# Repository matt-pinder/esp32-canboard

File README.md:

# ESP32-CANBoard
* ESP32-S3 Dual Core SoC
* MCP2562T CAN Transceiver (up to 1Mbps)
* 10x 5v Tolerant Inputs - Pressure Sensors, NTCs, etc
* 2x 5v Outputs - Fused at 500mA (Thermal Reset)
* USB-C for programming, with JTAG support for debugging
* ESD Protection on both USB and CAN
* JAE Automotive Connector (PCB Socket: MX23A18NF1, Cable Plug: MX23A18SF1)
* Optional pull-up resistors via fused 5v rail for each input (TH 6.3mm)
* Optional 120ohm CAN terminating resistor
* Configuration via web interface over WiFi
* Optional per-channel median filtering with selectable strength (none/low/med/high) to reduce noise
* Small PCB Footprint - 40mm x 60mm

## Build requirement

This project targets ESP-IDF 6.0.2. Activate the 6.0.2 environment before running any `idf.py` command; `main/idf_component.yml` and `dependencies.lock` enforce that toolchain version.

## Device Configuration

The board keeps its WiFi access point available continuously. To reduce idle memory use, the web server starts when a client associates with the access point and stops when that client disconnects.

Copy `main/inc/secrets.example.h` to the ignored `main/inc/secrets.h` and define infrastructure credentials with `KNOWN_WIFI_NETWORKS(X)`. Networks are tried in list order when ESP-NOW is disabled; the configuration access point remains available throughout.

| SSID | WPA2 Key | Web UI |
|:---|:---|:---|
| ESP32-CanBoard | canconfig | http://192.168.4.1 |

The web UI allows you to:

- View and edit per-channel settings (name, sensor type, pull-up, **filter level** dropdown, pressure calibration).
- Configure required CAN parameters - Base ID and bus speed.
- Configure CAN and ESP-NOW output, including optional CAN bus relay over ESP-NOW.
- Define reusable global Conditions from local sensor values or DBC-imported CAN signals, then reference those booleans from multiple Outputs and Triggered timers.
- Configure up to 8 Outputs using local sensor values, DBC-imported CAN signals, Conditions, startup timers, inline edge-triggered timers, PULSE lookup tables, and PWM duty lookup tables.
- Adjust pullup vref calculation voltage to allow for LDO regulator output/load.
- View current input voltages and calculated values in real time.
- Backup the entire configuration to a JSON file.
- Restore configuration from a previously exported JSON file.

| Function | Description |
|:----|:----|
| Save Config | Save current UI settings to the dedicated `config` NVS partition. Changes are validated, persisted and applied immediately. |
| Capture CAN (10s) | Stream every physical CAN data/RTR frame to the browser as a compact `.canlog` download. The board uses a bounded RAM queue and does not write the capture to flash. |
| Backup | Download one JSON snapshot containing the board configuration, reusable Conditions and Outputs. The filename is prefixed with `esp32-canboard-config-` and suffixed with the client timestamp in `ddmmyy-hhmmss` format. |
| Restore | Select a previously exported JSON file. The backend validates and applies the board configuration, Conditions and Outputs together while retaining their separate flash records. Legacy `rules` data is never imported. |
| Reboot Device | Reboots the device. |

**Notes:**
- CAN captures use a versioned little-endian binary format with a fixed header,
  20-byte frame records and a final loss/error trailer. Convert a downloaded
  capture to candump-style text with
  `python3 tools/decode_can_capture.py capture.canlog`, or add
  `--format csv -o capture.csv` for CSV. A missing `CANEND1` trailer means the
  browser connection ended before the capture completed.
- Board configuration is persisted as one current record in the dedicated `config` NVS partition. Conditions and Outputs are persisted together in the existing CRC-checked raw `rules` partition with atomic A/B writes; the partition location is unchanged even though the user-facing feature is now named Outputs.
- Only the current version-15 NVS board record is accepted. Pre-v15 NVS records and `/spiffs/config.bin` are deliberately unsupported after the verified 2026-10-05 aggregate backup.
- Normal `idf.py flash` updates the application and SPIFFS web assets, but does not write the dedicated `config` partition.
- `erase-flash`, whole-chip images, or explicitly flashing address `0x200000` will still erase configuration; ordinary application/partition-table flashing will not.
- After restoring a new configuration via the web UI the changes are applied immediately.
- The current checked-in recovery export is `config/esp32-canboard-config-051026-090441.json` (SHA-256 `25cc3a9ffa824093bf31c163345749b8048a588224715e386e33c09e3a9b6c78`). It contains all ten channels, two ESP-NOW clients, current GPS-source fields, Output schema version 4, one Condition, and three configured Outputs.

## Wi-Fi OTA

The VS Code custom task runs `scripts/build_and_ota.sh`. The script first checks
`/api/status`, rebuilds when either OTA artifact is missing or the sources are
newer, regenerates the embedded web asset as part of that build, and then
uploads both `build/esp32-canboard.bin` to `/api/ota` and `build/spiffs.bin` to
`/api/spiffs`. Connect to the `ESP32-CanBoard` access point before using the
default URL.

Set `ESP32_CANBOARD_OTA_URL` to override the target, for example:

```sh
ESP32_CANBOARD_OTA_URL=http://192.168.4.1/api/ota scripts/build_and_ota.sh
```

Set `ESP32_CANBOARD_SPIFFS_URL` as well only when the SPIFFS endpoint does not
share the application OTA host. The SPIFFS image must exactly match the existing
partition size and is SHA-256 checked in PSRAM before its partition is erased.
It is then written, read back and remounted. The HTTP API remains available if
SPIFFS cannot mount, allowing the image upload to be retried OTA.

The first combined OTA run from legacy firmware uploads the new application
first, waits for `/api/spiffs` to become available after reboot, and then sends
the web assets. Later runs send SPIFFS first and the application second, so only
the application update requires a reboot. No partition-table change or cable
flash is required when the installed firmware already supports `/api/ota`.

OTA requires the dual-slot partition table. After this change, perform one
normal UART `idf.py flash` only if the installed board does not already have
that table. The existing SPIFFS, `config`, and `rules` partition offsets are
unchanged; erasing the flash or writing those data offsets explicitly does not
preserve their contents.

## CAN Output

The device transmits five input-data frames followed by two Output command frames starting at the configured base ID. All frames use standard 11-bit CAN identifiers and DLC 8. Because the two Output frames occupy `Base ID + 5` and `Base ID + 6`, the configurable CAN base ID is restricted to `0x000` through `0x7F9`.

| CAN ID | Name | Payload |
|:---|:---|:---|
| Base ID | analogVoltage_1 | Inputs 0..3 as four uint16 (LSB,MSB) — bytes 0..7 (values in mV) |
| Base ID + 1 | analogVoltage_2 | Inputs 4..7 as four uint16 (LSB,MSB) — bytes 0..7 (values in mV) |
| Base ID + 2 | analogVoltage_3 | Inputs 8..9 as two uint16 (bytes 0..3), dynamic0 (bytes 4..5), dynamic1 (bytes 6..7) |
| Base ID + 3 | dynamicSignals_1 | dynamic2, dynamic3, dynamic4, dynamic5 as four 2-byte values (bytes 0..7) |
| Base ID + 4 | dynamicSignals_2 | dynamic6, dynamic7, dynamic8, dynamic9 as four 2-byte values (bytes 0..7) |
| Base ID + 5 | OutputBinaryCommands | Eight state bits, eight validity bits, eight pulse-mode bits, rolling counter, protocol version 2 |
| Base ID + 6 | OutputDutyCommands | Eight packed 7-bit duty percentages and the matching rolling counter |

The two Output frames are generated from one engine evaluation and one rolling counter. They are emitted in the order `Base + 5`, then `Base + 6`, after the five sensor frames at the configured 25 Hz or 50 Hz rate. When physical CAN is enabled both frames are sent to CAN, and both are also sent to every ESP-NOW client. The two Output CAN IDs are reserved: externally received frames colliding with either ID are not accepted as Output source data and are not re-relayed.

Encoding rules for dynamic values (one per input):

| Channel | Type | Encoding |
|:---|:---|:---|
|analogVoltage|-|unsigned uint16 = voltage * 1000 (resolution 0.001 V)|
|dynamicSignal|Raw|unsigned uint16 = **0** use analogVoltage signal instead|
|dynamicSignal|Pressure|unsigned uint16 = pressure_kPa * 100 (resolution 0.01 kPa)|
|dynamicSignal|NTC|signed int16 = temperature_C * 1 (°C as integer)|

Example DBCs for signal names and scaling are [dbc/esp32-canboard.dbc](dbc/esp32-canboard.dbc) and [dbc/esp32-canboard-outputs.dbc](dbc/esp32-canboard-outputs.dbc). The web UI also generates an Output DBC using the current base ID and configured Output labels.

### Outputs

There are eight configurable Outputs. Ordered cases retain the existing first-match `IF` / `ELSE IF` behavior; tests within one case are ANDed, while additional cases provide OR-through-ELSE-IF behavior. The tests only select which case runs: a matching PULSE case still derives its ON/OFF phase from the pulse lookup, and a matching PWM case still derives duty from the PWM lookup (with binary `state=1` only at exactly 100% duty). Existing OFF, ON, and PULSE actions retain their binary behavior. PWM is a fourth action and has its own numeric duty value; it does not replace or reinterpret the binary state, valid, or pulse signals.

For each timed PULSE lookup row, the cycle period must be greater than zero and the ON time must be between zero and the cycle period inclusive. `ON time = 0` means continuously OFF for that lookup point. The web editor exposes a dedicated `Permanently ON at/above` threshold instead of requiring a magic-looking final `ON time = cycle period` row. When configured, the UI stores that threshold as the final 1 s ON / 1 s period point in the existing PULSE lookup format, so no protocol or configuration-version change is required. Values at and above that threshold remain continuously ON.

Each PWM case selects one lookup source, a source hysteresis, and one through eight `{input_value, duty_percent}` rows. Input values must be finite and strictly increasing, and duties must be integer percentages from 0 through 100. Values below or above the lookup range clamp to the nearest endpoint. Values between rows are linearly interpolated and rounded to the nearest percentage. Duty is calculated immediately when a PWM case is entered, then held until the source differs from the accepted lookup input by **more than** the configured hysteresis. Entering another case, replacing configuration, startup, or source invalidation resets that PWM runtime state.

Source freshness and zero-confirmation rules apply equally to tests, PULSE lookup sources, and PWM lookup sources. A missing, stale, or not-yet-confirmed PWM source publishes `valid=0`, `state=0`, `pulse=0`, and duty `0`.

### Conditions

Up to 16 reusable named **Conditions** can be defined once and referenced by any Output case or Triggered timer. A Condition has one local-sensor or DBC-imported CAN source, a comparison and threshold, optional hysteresis, and a boolean result. Runtime state keeps `value` and `valid` separate: a Condition can therefore be `true`, `false`, or invalid. This avoids repeating CAN message/signal/comparison settings across multiple Outputs and reduces the chance of small configuration differences between rules.

Each Condition also defines what to do when its source later becomes unavailable or stale: `Invalid`, `False`, `True`, or `Hold last`. The stale policy is deliberately ignored until the Condition has first been established from at least one valid source sample. For example, `Engine running = DME1.RPM >= 600` with `When source stale = False` behaves as follows:

```text
Boot with no RPM ever received  -> Engine running is invalid
RPM received at 1000            -> Engine running = true
RPM CAN then disappears         -> Engine running = false
```

That distinction means ECU silence after a known-running engine can be used as a shutdown event without treating a board boot where the ECU was never present as an engine shutdown. A normal Output Condition test chooses whether the named Condition must be `True` or `False`; an invalid Condition retains the existing ordered-case unknown/invalid behavior rather than silently becoming false.

#### `Base ID + 5`: binary Output frame

Protocol version 2 keeps binary state, validity, and pulse mode independent. Only the low byte of each former 16-bit mask is used; the upper byte is required to be zero.

| Bytes | Encoding | Meaning |
|:---|:---|:---|
| 0 | uint8 bitmask | Output 1..8 state bits |
| 1 | uint8 | Reserved, must be `0` |
| 2 | uint8 bitmask | Output 1..8 validity bits |
| 3 | uint8 | Reserved, must be `0` |
| 4 | uint8 bitmask | Output 1..8 PULSE-mode bits |
| 5 | uint8 | Reserved, must be `0` |
| 6 | uint8 | Rolling counter, wraps `255 -> 0` |
| 7 | uint8 | Protocol version, exactly `2` |

For one Output, the action semantics are:

| Action / condition | state | valid | pulse | duty |
|:---|:---:|:---:|:---:|:---:|
| OFF | 0 | 1 | 0 | 0 |
| ON | 1 | 1 | 0 | 0 |
| PULSE, currently OFF | 0 | 1 | 1 | 0 |
| PULSE, currently ON | 1 | 1 | 1 | 0 |
| PWM, duty 0..99% | 0 | 1 | 0 | 0..99 |
| PWM, duty exactly 100% | 1 | 1 | 0 | 100 |
| Invalid / stale | 0 | 0 | 0 | 0 |

For OFF/ON/PULSE consumers, the safe applied binary state remains:

```text
applied binary state = valid AND state
```

For PWM, `state` is **not** a PWM-enabled flag. It is `1` only when the calculated duty is exactly 100%; duty 0 through 99 publishes `state=0`. Downstream configuration determines whether an Output should consume the duty field.

Examples for an otherwise empty binary frame (`CC` is the shared rolling counter):

| Situation | state / valid / pulse | `Base + 5` data bytes |
|:---|:---|:---|
| Output 1 continuously ON | `1 / 1 / 0` | `01 00 01 00 00 00 CC 02` |
| Output 1 validly OFF | `0 / 1 / 0` | `00 00 01 00 00 00 CC 02` |
| Output 2 in PULSE ON phase | `1 / 1 / 1` | `02 00 02 00 02 00 CC 02` |
| Output 2 in PULSE OFF phase | `0 / 1 / 1` | `00 00 02 00 02 00 CC 02` |
| Output 1 PWM at 50% | `0 / 1 / 0` | `00 00 01 00 00 00 CC 02` |
| Output 1 PWM at 100% | `1 / 1 / 0` | `01 00 01 00 00 00 CC 02` |
| Output invalid | `0 / 0 / 0` | `00 00 00 00 00 00 CC 02` |

#### `Base ID + 6`: duty frame

The duty frame packs eight unsigned 7-bit fields into bits 0 through 55. Values 101 through 127 are malformed and must be rejected by a consumer.

| Output | Start bit | Length | Valid values |
|:---:|:---:|:---:|:---:|
| 1 | 0 | 7 | 0..100 |
| 2 | 7 | 7 | 0..100 |
| 3 | 14 | 7 | 0..100 |
| 4 | 21 | 7 | 0..100 |
| 5 | 28 | 7 | 0..100 |
| 6 | 35 | 7 | 0..100 |
| 7 | 42 | 7 | 0..100 |
| 8 | 49 | 7 | 0..100 |
| Counter | 56 | 8 | 0..255 |

OFF, ON, and PULSE actions always publish duty `0`. Only the selected PWM action publishes a 0..100 value, and invalid PWM Outputs publish `0`. For example, Output 1 at 50% produces `32 00 00 00 00 00 00 CC`; Output 1 at 100% produces `64 00 00 00 00 00 00 CC`. A cross-byte example with duties `{0, 1, 99, 100, 1, 99, 100, 0}` produces `80 C0 98 1C 18 93 01 CC`.

A PWM consumer must treat `Base + 5` and `Base + 6` as one paired command. Accept duty only when both frames are correctly formed, both are fresh according to the consumer's timeout policy, and both counters match. A malformed frame, protocol-version error, duty outside 0..100, counter mismatch, or stale/missing partner must force applied duty to zero. Counter wrap from `255` to `0` is normal.

### Output timers

`Startup timer` is the original milliseconds-since-boot test. `Triggered timer` is an inline Output test and can be driven either directly from a local/CAN source or from a reusable Condition.

For a raw local/CAN trigger, the timer uses the configured comparison, threshold and optional hysteresis. It first has to observe that trigger false, which arms it; the next false-to-true transition starts the configured active period. Once active, the timer remains true until the period expires even if the raw trigger CAN source subsequently becomes stale or disappears.

For a Condition trigger, the editor selects a named Condition and whether the timer should trigger when it becomes `True` or `False`. The timer again arms only after first observing the opposite valid state. This combines with the Condition stale policy to handle ECUs that stop broadcasting before sending a low shutdown RPM. For example:

```text
Condition: Engine running
  DME1.RPM >= 600
  When source stale: False

Triggered timer:
  Engine running becomes False
  Active for 300 seconds
```

If the engine was observed running and its RPM broadcast then disappears, `Engine running` becomes false and the 300-second timer starts. If the board has never received a valid RPM sample, the Condition remains invalid and the timer does not arm or trigger.

Other AND tests remain live while a timer is active, so `OilTemp > 100 AND [Engine running becomes false, active for 300 s] -> ON` turns off early if oil temperature falls below the threshold, while the 300-second timer itself continues counting. Triggered timers are updated for every enabled Output before ordered case selection, so a timer in a lower-priority ELSE-IF case can still start while an earlier case is currently winning.

### Output configuration compatibility

The aggregate JSON property remains `outputs`, now at configuration version `5`. The schema contains `signal_timeout_ms`, used CAN `sources`, a sparse `conditions` array numbered 1 through 16, and a sparse `outputs` array numbered 1 through 8. CAN sources can carry DBC-derived physical range and raw-invalid-value metadata. Conditions serialize `label`, `source_name`, comparison/hysteresis fields, and `stale_behavior`. Output Condition tests reference the Condition by name; Condition-driven Triggered timers serialize `trigger_condition_name`, the expected boolean state, and `trigger_duration_ms`. Raw-source Triggered timers retain their direct `source_name`, comparison/hysteresis and duration fields. PWM cases continue to serialize `pwm_source_name`, `pwm_hysteresis`, and `pwm_points`.

Version 4 JSON imports and compact raw-partition records remain accepted. Their CAN sources migrate with validity checks disabled until a reference DBC is selected and Outputs are saved. Version 5 records persist the DBC range and `GenSigInvalidValue` metadata in the same CRC-checked A/B record as Outputs, Conditions and CAN sources. Frames carrying an invalid raw value or a decoded value outside the enabled range do not replace the last accepted value or refresh its timestamp, allowing the configured stale behavior (including `Hold last`) to take effect after `signal_timeout_ms`. No partition-table change is required.

Pre-Output rule records remain deliberately incompatible and are not translated: on first boot with one of those old records, firmware initializes eight empty Outputs and no Conditions and commits the empty current record into both CRC-checked A/B slots. The physical raw partition remains named `rules` and remains at the same partition-table location.

Aggregate restore requires a valid current `outputs` object. Missing, malformed, or incompatible Output data and invalid CAN base IDs are rejected rather than reset, clamped, guessed, or translated. Legacy top-level `rules` backups are unsupported.

Live status is exposed as `/api/live_values.conditions` for configured Conditions and `/api/live_values.outputs` for configured Outputs. Condition status includes boolean value, validity, whether a valid source has ever established the Condition, source freshness and source-invalid reason. Output live status still includes `duty_percent` for the selected valid PWM case.

### E46 M3 MK60 cluster emulator (capture-first)

The firmware contains an opt-in MK60 request/response service for cars where
the original instrument cluster has been removed. It is disabled by default
and has no factory response payload: capture the car first with the standalone
listen-only logger in [`tools/mk60-can-capture`](tools/mk60-can-capture).

The `mk60_emulator` object is included in configuration backup/import JSON. A
profile contains the exact standard data frames observed after the MK60's
standard `0x610` RTR request. Only `0x610`, `0x613`, `0x615`, `0x316`, and
`0x329` are accepted, the first response must be `0x610`, and emulation can
only be enabled with a complete profile at 500 kbit/s.

```json
"mk60_emulator": {
  "enabled": false,
  "trigger_id": 1552,
  "trigger_dlc": 8,
  "responses": []
}
```

Populate `responses` from repeatable connected/disconnected captures. Each
entry has `id`, `dlc`, `delay_before_ms`, and an eight-element `data` byte
array. Do not copy example payloads from the internet or enable the feature
until the bytes and timing have been verified on the target MK60. A CAN
transmit error or bus-off condition latches the emulator off until its profile
is reapplied or the board restarts.

### CAN relay over ESP-NOW

When ESP-NOW and **Relay CAN bus** are enabled for a client, externally received CAN frames are encoded into the same portable raw-CAN batch protocol as the board's own frames. The wire format is not an in-memory `twai_message_t`: version 1 uses a 14-byte little-endian header followed by one to eighteen fixed 13-byte CAN records, for a maximum packet size of 248 bytes. Physical CAN transmission of the board's own sensor frames may remain disabled; the TWAI controller and CAN speed setting remain active while relay reception, MK60 emulation, or externally sourced Output rules need CAN input.

Relay traffic is best-effort and lower priority than the board's sensor and GPS output. The bounded 128-frame queue discards its oldest frame when full instead of blocking ADC sampling or locally generated transmissions. Frames are batched for up to 5 ms. Each client has its own sequence and delivery state; after three consecutive delivery failures only that client backs off to one probe per second, while healthy clients continue at normal rate.

Each configured ESP-NOW client can also have an optional human-readable label. The label is persisted with the board configuration and included in configuration export/import JSON alongside that client's MAC address and relay setting. Existing configurations migrate with blank client labels.

ESP-NOW and the local configuration access point use Wi-Fi channel 1. The receiving ESP-NOW device must also operate on channel 1 and must give this board its station MAC as the permitted sender. Configure the receiver's station MAC as a client here; enable **Relay CAN bus** for that client only when physical CAN frames received by this board must also reach it. Locally generated sensor, Output, and GPS frames are sent to every configured client. ESP-NOW is unencrypted, so receiver MAC filtering rejects unrelated senders but is not cryptographic authentication.

While ESP-NOW is enabled, this firmware deliberately keeps the station radio on channel 1 and does not join a configured infrastructure network. The configuration SoftAP remains available and owns the fixed radio channel.

### Connected repository contract

| Repository | Role | ESP-NOW/CAN requirement |
|:---|:---|:---|
| `esp32-r8` | R8 dashboard/logger | Add its reported station MAC as a client; it defaults to permitting canboard STA MAC `DC:DA:0C:3B:B2:0C`. It decodes classic standard, non-RTR data frames only. |
| `esp32-e36` | E36 dashboard/logger | Add its reported station MAC as a client; it defaults to permitting canboard STA MAC `DC:DA:0C:3C:E8:08`. It decodes classic standard, non-RTR data frames only. |
| `esp32-output` | Output/PWM receiver and optional GPS responder | Add its displayed station MAC as a client. Output command frames use `Base + 5` and `Base + 6`; GPS response uses the separate 44-byte `GP` version-1 snapshot. |

The raw-CAN batch format is version 1 in all four repositories. Dashboard DBCs, telemetry schemas, RTCs, UI projects, hardware pins, NVS namespaces, and default sender MACs are vehicle profiles and are intentionally not interchangeable.

## Dragy GPS Output

When GPS is enabled, the board scans for the configured Dragy BLE MAC, connects to service `FD00`, performs the `FD03` challenge response, and decodes checksum-valid UBX NAV-PVT packets from `FD02`. Valid fixes are published at the GPS update rate; a connected no-fix stream publishes only the status frame, limited to 1 Hz. BLE discovery, decoding, and publishing run independently from ADC sampling and the existing sensor transmit task.

Dragy output uses six standard 11-bit CAN frames starting at the configured GPS base ID. All multi-byte values are little-endian. Position and motion fields retain their native UBX scaling, altitude/UTC are compactly repacked, and IMU fields contain unscaled signed raw counts.

| CAN ID | Bytes | Type | Value |
|:---|:---|:---|:---|
| GPS Base ID | 0 | uint8 | UBX fix type (`0` no fix, `2` 2D, `3` 3D, `4` GNSS + dead reckoning) |
| GPS Base ID | 1 | uint8 | UBX NAV-PVT flags; bit 0 is `gnssFixOK` |
| GPS Base ID | 2 | uint8 | Satellite count |
| GPS Base ID | 3 | uint8 | Dragy battery percent, or `0xFF` when unavailable |
| GPS Base ID | 4..7 | uint32 | Horizontal accuracy in mm |
| GPS Base ID + 1 | 0..3 | uint32 | Ground speed in mm/s |
| GPS Base ID + 1 | 4..7 | int32 | Heading of motion in degrees x 100,000 |
| GPS Base ID + 2 | 0..3 | int32 | Latitude in degrees x 10,000,000 |
| GPS Base ID + 2 | 4..7 | int32 | Longitude in degrees x 10,000,000 |
| GPS Base ID + 3 | bits 0..21 | int22 | Mean-sea-level altitude in cm |
| GPS Base ID + 3 | bits 22..31 | uint10 | UTC millisecond component (`0..999`) |
| GPS Base ID + 3 | bits 32..63 | uint32 | Unix UTC seconds |
| GPS Base ID + 4 | 0..2 | uint24 | FD05 sample counter |
| GPS Base ID + 4 | 3 | uint8 | FD05 record marker (`0xE1`) |
| GPS Base ID + 4 | 4..5 | int16 | Raw accelerometer X |
| GPS Base ID + 4 | 6..7 | int16 | Raw accelerometer Y |
| GPS Base ID + 5 | 0..1 | int16 | Raw accelerometer Z |
| GPS Base ID + 5 | 2..3 | int16 | Raw gyroscope X |
| GPS Base ID + 5 | 4..5 | int16 | Raw gyroscope Y |
| GPS Base ID + 5 | 6..7 | int16 | Raw gyroscope Z |

The Dragy BLE handshake and stream format are based on the experimental [DragyDash ESP32 protocol notes](https://github.com/jremick/dragy-dash-esp32/blob/main/docs/DRAGY_PROTOCOL.md).

### Dragy update-rate probe

[`tools/dragy_rate_probe.py`](tools/dragy_rate_probe.py) connects from macOS or another Bleak-compatible host, inventories the `FD00` characteristics, performs the normal handshake, and reassembles every checksum-valid UBX message received through `FD02`. It reports both host arrival rate and the rate derived from NAV-PVT `iTOW`, and separately detects `UBX-HNR-PVT` if that message ever appears.

To test whether the mobile-app setting persists in the Dragy, select a rate in the app, disconnect the app completely, and make a capture. Repeat for each setting:

```sh
python3 -m pip install bleak
python3 tools/dragy_rate_probe.py --label 10Hz --duration 15 --output dragy-10hz.json
python3 tools/dragy_rate_probe.py --label 20Hz --duration 15 --output dragy-20hz.json
python3 tools/dragy_rate_probe.py --label 25Hz --duration 15 --output dragy-25hz.json
python3 tools/dragy_rate_probe.py --compare dragy-10hz.json dragy-20hz.json dragy-25hz.json
```

Use `--name` if the advertised name differs from `DRGPR-7E084E`. The comparison shows NAV-PVT rate and delta distributions, all observed UBX class/message IDs, HNR-PVT counts, and any changed readable characteristic values. A persisted output-rate change proves the setting is stored by the Dragy, but identifying the command used to change it still requires capturing the app's BLE writes.

The `FD00` service also exposes writable characteristic `FD01`, which testing confirmed is a transparent UBX command ingress paired with notify-only telemetry characteristic `FD02`. A `UBX-MON-VER` poll sent to FD01 returned the following receiver identity through FD02:

- Module: MAX-M10S
- Firmware: SPG 5.10
- Protocol: 34.10
- Enabled systems reported by the firmware: GPS, GLONASS, Galileo, BeiDou, SBAS, and QZSS

The command path can be checked without changing configuration by polling the receiver version:

```sh
python3 tools/dragy_rate_probe.py --probe-command-path --duration 5 --output dragy-command-probe.json
```

The summary should contain message `0A/04` and report the command path as confirmed. An experimental rate can then be applied to the receiver's RAM layer only:

```sh
python3 tools/dragy_rate_probe.py --set-rate 25 --duration 15 --output dragy-set-25hz.json
```

This sends `CFG-RATE-MEAS=40 ms` and `CFG-RATE-NAV=1` using `UBX-CFG-VALSET`. The 10 Hz and 20 Hz choices use 100 ms and 50 ms respectively. The receiver returned `UBX-ACK-ACK` for both configuration messages and changed its NAV-PVT iTOW cadence accordingly. The command deliberately does not select the battery-backed RAM or flash layers, so it does not permanently write receiver configuration.

At 20 Hz and 25 Hz, testing found occasional complete navigation epochs missing from FD02 even though NAV-PVT iTOW confirmed the configured receiver rate. To test whether the periodic NAV-DOP and larger NAV-SAT messages cause that loss, disable both while setting 25 Hz:

```sh
python3 tools/dragy_rate_probe.py \
  --set-rate 25 \
  --disable-extra-nav \
  --duration 30 \
  --output dragy-25hz-pvt-only.json
```

The probe first reads the PVT, DOP, and SAT message-output rates for I2C, UART1, and SPI so the active receiver interface can be identified. It then disables DOP and SAT on all three interfaces in the RAM layer. A successful test should report eight `UBX-ACK-ACK` messages—two rate settings and six message-output settings—no `01/04` or `01/35` messages after the short transition, and NAV-PVT host rate close to 25 Hz with almost exclusively 40 ms iTOW deltas.

Testing identified I2C as the active Dragy receiver interface: NAV-PVT had rate 1 and NAV-DOP/NAV-SAT each had rate 10. Disabling DOP and SAT removed those messages after the buffered transition but did not improve NAV-PVT completeness: delivery remained about 24 Hz with periodic 80 ms iTOW gaps. Earlier NAV-SAT captures showed GPS, Galileo, BeiDou, and GLONASS all active. The remaining missed epochs therefore appear unrelated to competing UBX output bandwidth; a separate single-GNSS test is required to distinguish MAX-M10S navigation workload from Dragy's BLE forwarding limit.

Run that single-GNSS experiment with:

```sh
python3 tools/dragy_rate_probe.py \
  --single-gnss \
  --set-rate 25 \
  --disable-extra-nav \
  --duration 60 \
  --output dragy-25hz-gps-only.json
```

The probe first reads the RAM constellation settings, then keeps GPS enabled while disabling Galileo, BeiDou, and GLONASS in one RAM-only `UBX-CFG-VALSET`. QZSS and SBAS are left unchanged. Changing signal configuration restarts the GNSS subsystem, so the probe waits before applying the rate and message-output settings. Testing observed eleven ACK messages: two configuration queries, one signal configuration, two rate settings, and six DOP/SAT output settings.

The GPS-only test produced a complete post-configuration stream: 1,498 NAV-PVT frames over approximately 59.8 seconds, with all 1,497 iTOW intervals exactly 40 ms and a measured host arrival rate of approximately 25 Hz. The few non-40 ms intervals in the full capture occurred before the final configuration acknowledgement, during the GNSS restart and rate transition. This confirms that the earlier missing epochs were caused by attempting 25 Hz with GPS, Galileo, BeiDou, and GLONASS all enabled, rather than by FD02 BLE throughput.

### Dragy Pro IMU capture (experimental)

Testing with a Dragy Pro DRG71 found an undocumented IMU notification stream on characteristic `FD05`. Notifications contain one or more 16-byte records:

| Bytes | Encoding | Observed value |
|:---|:---|:---|
| 0..2 | uint24, big-endian | Sample counter, increasing by 12 per sample |
| 3 | uint8 | Record marker (`0xE1`) |
| 4..9 | 3 x int16, big-endian | Accelerometer X/Y/Z |
| 10..15 | 3 x int16, big-endian | Gyroscope X/Y/Z |

[`tools/dragy_imu_capture.py`](tools/dragy_imu_capture.py) connects directly from a host using [Bleak](https://github.com/hbldh/bleak), performs the existing `FD03` challenge response, subscribes to `FD05`, and writes the decoded samples to CSV:

```sh
python3 -m pip install bleak
python3 tools/dragy_imu_capture.py --duration 20 --output dragy_imu.csv
```

The observed stream rate is approximately 14.5 Hz. The CSV's acceleration conversion currently uses a provisional scale of 4096 counts/g; gyroscope values remain raw until the scale and axis orientation have been calibrated. Disconnect the Dragy mobile app and ESP32 first because the Dragy may only accept one BLE central connection at a time.

When GPS is enabled in the ESP32 configuration, the firmware subscribes to `FD05` alongside `FD02` and publishes every queued IMU record on CAN IDs `GPS Base ID + 4` and `GPS Base ID + 5`. The full counter, marker, and six raw channels are retained so a CAN log can be aligned with a second Dragy's app output for calibration.

The example DBC includes all six Dragy messages at `0x650` through `0x655`, corresponding to the default GPS base ID of `0x650`. GPS fields are converted to metres, m/s, degrees, and seconds by the DBC, while IMU fields remain raw counts. Update those message IDs if a different GPS base ID is configured.

### ESP-NOW GPS response source

The GPS source can instead be set to **ESP-NOW response**. Select one of the
configured ESP-NOW clients and a freshness timeout from 100 to 60000 ms. The
GPS enable switch and GPS base CAN ID are shared with Dragy; the Dragy BLE MAC,
scan control, and update rate are retained in configuration but only used when
Dragy is selected. Version-14 configuration is migrated to version 15 with
Dragy selected, so existing GPS and BLE settings are preserved.

The selected output replies with one fixed 44-byte, little-endian version-1 snapshot:

| Bytes | Value |
|:---|:---|
| 0..1 | ASCII magic `GP` |
| 2 | Protocol version `1` |
| 3 | Flags: fix valid, time valid, course valid |
| 4..5 | Sample sequence |
| 6..9 | Output uptime in milliseconds |
| 10..13 | Sample age in milliseconds at transmission |
| 14..17 | Unix UTC seconds |
| 18..21, 22..25 | Latitude and longitude in `1e-7` degrees |
| 26..29 | Speed in millimetres per second |
| 30..33 | Heading in `1e-5` degrees |
| 34..37 | Mean-sea-level altitude in millimetres |
| 38 | Satellites used |
| 39 | NMEA GGA fix quality |
| 40..41 | HDOP multiplied by 100 |
| 42..43 | UTC millisecond component (`0..999`) |

Packets must have the exact length and known flags, pass all field range checks,
and come from the selected client. Sequence comparison handles uint16 wrap;
lower sender uptime identifies a sender restart. Snapshots are RAM-only.

A fresh valid snapshot is replayed at the normal 25 or 50 Hz CAN transmit
cadence on the configured base ID through `can_transmit_frame()`, so the same
frames reach enabled TWAI and every configured ESP-NOW client. Frames `base+0`
through `base+3` contain status, speed/heading, position, and altitude/UTC.
Fix type is 2 for a valid matched RMC/GGA epoch. Satellites and altitude come
from GGA, while UBX-only flags, battery, and horizontal accuracy remain zero;
HDOP is not misrepresented as horizontal accuracy. A fresh invalid fix, missing response, or expired sample
publishes only the repeated fix-invalid status frame until a fresh valid fix
arrives. Dragy navigation and IMU publishing are unchanged when Dragy is the
selected source.

The host codec tests exercise exact-length, flag, range, sequence, restart, and
malformed-packet handling. A successful firmware build verifies compilation and
linkage only; UART traffic, radio retry behaviour, TWAI output, timing, and GPS
electrical operation still require hardware acceptance testing.

## Schematic
[View PDF](docs/esp32-canboard-schematic.pdf)

## Images

## Connector Pinout
|Pin|Function|Additional Information|
|:---:|:---|:---|
|1|12v Supply||
|2|5v Sensor Supply|500ma Thermal Fuse|
|3|5v Sensor Supply|500ma Thermal Fuse|
|4|Input 6||
|5|Input 7||
|6|Input 8||
|7|Input 9||
|7|Input 10||
|9|CAN High||
|10|Ground||
|11|Ground||
|12|Ground||
|13|Input 1||
|14|Input 2||
|15|Input 3||
|16|Input 4||
|17|Input 5||
|18|CAN Low||

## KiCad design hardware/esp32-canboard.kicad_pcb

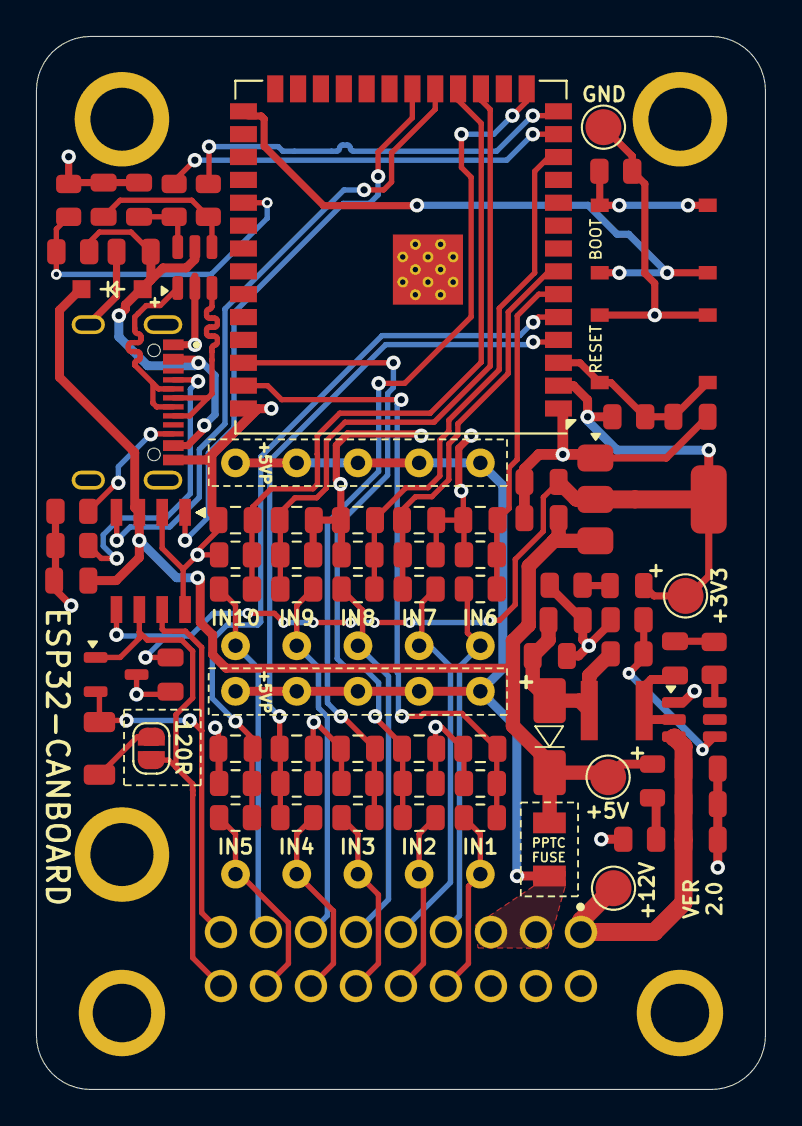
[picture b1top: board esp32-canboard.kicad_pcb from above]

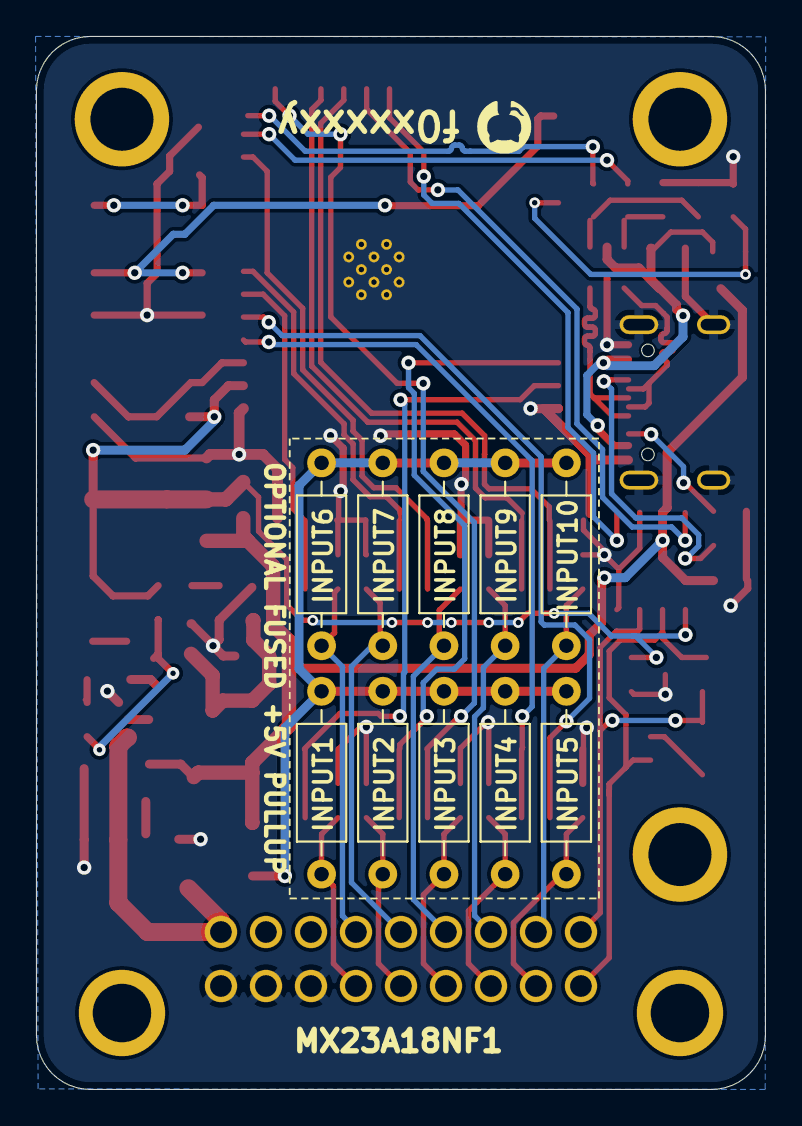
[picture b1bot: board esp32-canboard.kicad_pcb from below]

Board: 2 copper layers, 40.5 x 58.5 mm, 92 parts (10 on the bottom side), 50 nets.

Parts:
C1, C2, C8, C15, C16, C17, C18, C19, C20, C21, C22, C23, C24: 10uF; C_0805_2012Metric
C3, C4, C7, C9, C10, C12, C14: 100nF; C_0805_2012Metric
C5, C6: 22uF; C_0805_2012Metric
C11, C13: 20pF; C_0805_2012Metric
CONN1: MX23A18NF1
CONN2: KH-TYPE-C-16P; KINGHELM_KH-TYPE-C-16P
D1: Scho (SS33); D_SMA
D2: Sch (DSK110); DIODE-SOD-123
ESD1: USBLC6-2SC6; SOT-23-6
ESD2: NUP2105LT1G; SOT-23-3
F1: 1206L050YR; 1206L05015YR
IC1: MCP2562T-E_SN; SOIC127P600X175-8N
JP2: TERM_SB; SolderJumper-2_P1.3mm_Open_RoundedPad1.0x1.5mm
L1: 5.6uH; SMNR4020-5R6MT
LED1: 0805_Green; LED_0805_2012Metric
LED2: 0805_Yellow; LED_0805_2012Metric
MH1: MH1
MH2: MH2
MH3: MH3
R1: 33R; R_0805_2012Metric
R2: 56K; R_0805_2012Metric
R3, R6, R8, R9, R16, R20, R23, R26, R29, R40, R41, R42, R43, R44: 10K; R_0805_2012Metric
R4: 300R; R_0805_2012Metric
R5: 120R; R_0805_2012Metric
R7: 120R 0.25W; R_1206_3216Metric
R10, R15, R19, R22, R25, R28, R35, R36, R37, R38, R39: 4K7; R_0805_2012Metric
R11, R12: 22R; R_0805_2012Metric
R13, R14: 5K1; R_0805_2012Metric
R17, R18, R21, R24, R27, R30, R31, R32, R33, R34: OPTIONAL; R_Axial_DIN0207_L6.3mm_D2.5mm_P10.16mm_Horizontal
SW1: BOOT; SW_TS-1187A-B-A-B
SW2: RESET; SW_TS-1187A-B-A-B
TP1: 5VTP; TestPoint_Pad_D2.0mm
TP2: GND; TestPoint_Pad_D2.0mm
TP3: 3V3TP; TestPoint_Pad_D2.0mm
TP4: 12VTP; TestPoint_Pad_D2.0mm
U1: TPS56339DDCR; SOT-23-6
U2: LD1117S33CTR; SOT-223
U3: ESP32-S3-WROOM-1U-N8R8; ESP32-S3-WROOM-1U

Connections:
+3V3: C8.1, C12.1, IC1.5 (VIO), LED2.2 (A), R8.1, TP3.1, U2.2 (VOUT), U2.4 (VOUT), U3.2 (3V3)
+5V: C7.1, C10.1, D1.1 (K), D2.1 (K), F1.1, IC1.3 (VDD), LED1.2 (A), TP1.1, U2.3 (VIN)
+5VP: CONN1.2, CONN1.3, F1.2, R17.1, R18.1, R21.1, R24.1, R27.1, R30.1, R31.1, R32.1, R33.1, R34.1
+12V: C1.1, C2.1, C3.1, CONN1.1, TP4.1, U1.3 (VIN)
AIN1: C15.1, R15.1, R16.1, U3.39 (IO1)
AIN2: C16.1, R19.1, R20.1, U3.38 (IO2)
AIN3: C17.1, R22.1, R23.1, U3.15 (IO3)
AIN4: C18.1, R25.1, R26.1, U3.4 (IO4)
AIN5: C19.1, R28.1, R29.1, U3.5 (IO5)
AIN6: C20.1, R35.1, R40.1, U3.6 (IO6)
AIN7: C21.1, R36.1, R41.1, U3.7 (IO7)
AIN8: C22.1, R37.1, R42.1, U3.12 (IO8)
AIN9: C23.1, R38.1, R43.1, U3.17 (IO9)
AIN10: C24.1, R39.1, R44.1, U3.18 (IO10)
CAN1_H: CONN1.9, ESD2.2, IC1.7 (CANH), R7.2
CAN1_L: CONN1.18, ESD2.1, IC1.6 (CANL), JP2.1 (A)
CAN1_RX: IC1.4 (RXD), U3.19 (IO11)
CAN1_TX: IC1.1 (TXD), U3.20 (IO12)
GND: C1.2, C2.2, C3.2, C5.2, C6.2, C7.2, C8.2, C9.1, C10.2, C11.2, C12.2, C13.2, C14.2, C15.2, C16.2, C17.2, C18.2, C19.2, C20.2, C21.2, C22.2, C23.2, C24.2, CONN1.10, CONN1.11, CONN1.12, CONN2.A1_B12 (GND), CONN2.A12_B1 (GND), CONN2.SH1 (SHIELD), CONN2.SH2 (SHIELD), CONN2.SH3 (SHIELD), CONN2.SH4 (SHIELD), ESD1.2 (GND), ESD2.3, IC1.2 (VSS), IC1.8 (STBY), R3.2, R4.1, R5.1, R6.2, R9.2, R13.2, R14.2, R16.2, R20.2, R23.2, R26.2, R29.2, R40.2, R41.2, R42.2, R43.2, R44.2, SW2.1, TP2.1, U1.1 (GND), U2.1 (GND), U3.1 (GND), U3.40 (GND), U3.41 (GND)
INPUT1: CONN1.13, R15.2, R17.2
INPUT2: CONN1.14, R18.2, R19.2
INPUT3: CONN1.15, R21.2, R22.2
INPUT4: CONN1.16, R24.2, R25.2
INPUT5: CONN1.17, R27.2, R28.2
INPUT6: CONN1.4, R30.2, R35.2
INPUT7: CONN1.5, R31.2, R36.2
INPUT8: CONN1.6, R32.2, R37.2
INPUT9: CONN1.7, R33.2, R38.2
INPUT10: CONN1.8, R34.2, R39.2
unnamed: C4.2, R1.1
unnamed: C11.1, ESD1.4 (I/O2), R11.2
unnamed: C13.1, ESD1.6 (I/O1), R12.2
unnamed: CONN2.A5 (CC1), R14.1
unnamed: CONN2.B5 (CC2), R13.1
unnamed: CONN2.A6 (D+), CONN2.B6 (D+), ESD1.3 (I/O2)
unnamed: CONN2.A7 (D-), CONN2.B7 (D-), ESD1.1 (I/O1)
unnamed: C5.1, C6.1, D1.2 (A), L1.1, R2.2
unnamed: JP2.2 (B), R7.1
unnamed: LED1.1 (K), R4.2
unnamed: LED2.1 (K), R5.2
unnamed: R6.1, SW1.1
unnamed: R1.2, U1.6 (BOOT)
unnamed: R2.1, R3.1, U1.4 (FB)
unnamed: C4.1, L1.2, U1.2 (SW)
unnamed: C9.2, R8.2, SW2.2, U3.3 (EN)
unnamed: SW1.2, U3.27 (IO0)
unnamed: R9.1, R10.1, U3.31 (IO38)
unnamed: R11.1, U3.14 (USB_D+)
unnamed: R12.1, U3.13 (USB_D-)
USB_VBUS: C14.1, CONN2.A4_B9 (VBUS), CONN2.A9_B4 (VBUS), D2.2 (A), ESD1.5 (VBUS), R10.2

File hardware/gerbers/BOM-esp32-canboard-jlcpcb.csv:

Comment,Designator,Footprint,LCSC
10uF,"C1,C2,C8,C15,C16,C17,C18,C19,C20,C21,C22,C23,C24",Capacitor_SMD:C_0805_2012Metric,C15850
100nF,"C3,C4,C7,C9,C10,C12,C14",Capacitor_SMD:C_0805_2012Metric,C49678
22uF,"C5,C6",Capacitor_SMD:C_0805_2012Metric,C45783
20pF,"C11,C13",Capacitor_SMD:C_0805_2012Metric,C1798
KH-TYPE-C-16P,CONN2,KH-TYPE-C-16P:KINGHELM_KH-TYPE-C-16P,C709357
Scho (SS33),D1,Diode_SMD:D_SMA,C28646294
Sch (DSK110),D2,TO_SOT_SMD:DIODE-SOD-123,C22466354
USBLC6-2SC6,ESD1,Package_TO_SOT_SMD:SOT-23-6,C7519
NUP2105LT1G,ESD2,Package_TO_SOT_SMD:SOT-23-3,C2890118
MCP2562T-E_SN,IC1,MCP2562T-E_SN:SOIC127P600X175-8N,C191417
5.6uH,L1,SMNR4020-5R6MT:SMNR4020-5R6MT,C467062
0805_Green,LED1,LED_SMD:LED_0805_2012Metric,C2297
0805_Yellow,LED2,LED_SMD:LED_0805_2012Metric,C2296
33R,R1,Resistor_SMD:R_0805_2012Metric,C17634
56K,R2,Resistor_SMD:R_0805_2012Metric,C17756
10K,"R3,R6,R8,R9,R16,R20,R23,R26,R29,R40,R41,R42,R43,R44",Resistor_SMD:R_0805_2012Metric,C17414
300R,R4,Resistor_SMD:R_0805_2012Metric,C17617
120R,R5,Resistor_SMD:R_0805_2012Metric,C17437
120R 0.25W,R7,Resistor_SMD:R_1206_3216Metric,C17909
4K7,"R10,R15,R19,R22,R25,R28,R35,R36,R37,R38,R39",Resistor_SMD:R_0805_2012Metric,C17673
22R,"R11,R12",Resistor_SMD:R_0805_2012Metric,C17561
5K1,"R13,R14",Resistor_SMD:R_0805_2012Metric,C27834
SWITCH,"SW1,SW2",TS-1187A-B-A-B:SW_TS-1187A-B-A-B,C318884
TPS56339DDCR,U1,Package_TO_SOT_SMD:SOT-23-6,C2071106
LD1117S33CTR,U2,Package_TO_SOT_SMD:SOT-223,C35879
1206L050YR,F1,1206L050YR:1206L050YR,C163512

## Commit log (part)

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2025-05-24 Initial
2025-06-25 Remove legacy ADC reference
2025-06-27 Sensor calibrations
2025-06-27 Output Pressures
2025-06-27 Added pullup vref compensation
2025-06-27 Corrected pullup rear silkscreen numbering
2025-06-27 Change cast on cpuTemp
2025-06-27 Value changes
2025-06-27 Scaling
2025-06-27 Change NTC calculation
2025-06-27 NTC Table
2025-06-27 Clamp maximum temperature
2025-07-03 Calibrations and CAN Outputs
2025-07-03 Remove build
2025-07-06 Return pressure 0 if voltage 0
2025-07-06 Corrected BASE+4
2025-07-06 Change turbo pressure to bar
2025-07-09 Added optional ADC filtering
2025-07-11 Added function comments
2025-07-12 Case STLs
2025-07-13 Charge Cooler Quadratic Equation
2025-07-14 Switch Turbo Oil Pressure Sensor
2025-07-14 Move processing into tasks
2025-07-15 Scaled Pressure Changes
2025-07-15 Corrected CAN Message Array
2025-07-15 Scaling changes
2025-07-18 TMAP and CC Pressure Changes
2025-07-26 Changing for E36
2025-07-28 Updated DBC
2025-07-31 TMAP Changes
2025-08-02 NTC Changes
2025-08-13 Pre r8 work
2025-08-13 first attempt
2025-08-15 added Matts espnow code
2025-08-17 Task Stack Sizes
2025-10-13 CC Changes
2026-01-14 Initial release
2026-01-14 Output changes
2026-01-14 Moved CAN init
2026-01-16 Various fixes.
2026-01-16 Update docs
2026-01-16 Moved vref to config.
2026-01-16 Docs update
2026-01-16 Added NTC sensor
2026-02-03 before back to e36
2026-02-16 Custom NTC with pullup set for 5015
2026-02-16 addition of custom ntc
